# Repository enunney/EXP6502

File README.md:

# EXP6502
6502 based expandable computer.

## Specifications

- W65C02 CPU @ 8MHz
- 64 kB SRAM
- 32 kB EEPROM (read only)
- 7 general purpose expansion ports
- Bank switching with access to up to 160 kB of memory
- W65C22 Versatile Interface Adapter
- Software controllable glitchless clock switching (8 MHz / fraction of 8 MHz)
- Built-in beeper speaker and LED
- 5 built-in push buttons with interrupt capability

## Architecture
### Block diagram

The CPU address and data buses are directly connected to the onboard memory and peripherals. Tristate buffers isolate the local buses from the expansion ports.
CMOS logic ICs decode the address bus as well as the status of the control register to provide control signals for each component.

### Memory map

The lower half of the address space contains 32 kB of RAM (the low RAM) and the I/O space. The I/O space sits
between $6000 and $6FFF. It can be switched out to access the 4 kB of RAM located at the same memory addresses.

The I/O space is made of two parts. The bottom one is divided in 8 pages, each of these controlling one I/O
peripheral. The first I/O page is reserved for the built in VIA. The 7 others are each attributed to a different
expansion port. The top part of the I/O space, IOH, is available on every expansion port, in case they need more I/O
addresses.

The upper half of the address space is divided in two blocks, each of them is multiplied in 4 banks. One bank in each
block can be selected at a time, and the two blocks can have a different bank selected.

The first bank gives access to the ROM of the computer, it is selected by default at start up or after reset.
The second one gives access to 32 kB of RAM, the high RAM.
The third and fourth ones give access to memory placed on the expansion ports. The chip select signals of these
banks are accessible on any expansion port.

The bank switching in the lower half of the address space is controlled by the RIO signal, bit 3 of the control register.
It allows switching the window between $6000 and $6FFF to the I/O space, when RIO is low, or to the low RAM,
when RIO is high.

The bank switching in the upper half of the address space is controlled by the LB0, LB1, HB0 and HB1 signals, bits 4 to
7 of the control register. The bits LB0 and LB1 control the bank switching in the bottom block (\$8000 to \$BFFF). HB0
and HB1 control the switching in the top block (\$C000 to \$FFFF).
- The first bank, bank 0, is mapped to the ROM, in the two blocks.
- The bank 1, is mapped in the two blocks to the high RAM.
- The bank 2 enables the external high memory 0, EXT0HI in the top block and the external low memory 0, EXT0LO in the bottom block.
- The bank 3 enables the external high memory 1, EXT1HI in the top block and the external low memory 1, EXT1LO in the bottom block.

### Expansion port

The computer has 7 general purpose expansion ports.
They give access to buffered versions of the address and data buses of the computer, to various control signals of
the microprocessor and to the selecting signals for the external memory banks. They also have access to some pins
of the VIA.

The expansion ports have access to the main clock, φ2, as well as the oscillator clock and the divided clock. This
feature allows an expansion card to keep using one of these clocks while the computer has switched to another one,
for instance for slow peripherals that couldn’t handle the oscillator frequency. It is worth noting that the CPU can’t
access these peripherals while the clocks are different, as it would have an unpredictable behavior.

Any expansion port can take control of the computer, by setting low the EXTCTLB signal, which disables the busses of
the CPU and reverses the direction of the address and data buffers. The RDY signal should be put low at the same
time to effectively halt the CPU.

The expansion port 1 has an additional two pins header socket placed next to it. It is intended to be connected to the
read and write pins of a TFT LCD screen (controlled by an ILI9341 IC or compatible) for write only access when the
port 1 is connected to such a screen.

The pinout of the expansion ports and the function of each pin can be found in the technical reference manual.

### Control register

The control register allows the software to switch the memory banks, to change the clock speed and to directly
control an LED and the beeper speaker.
It is located at address $0000 of the address space, in the zero page of the 6502 microprocessor, to allow faster
access.
The function of each of its bits is given below:

- Bit 0: CPULED
→ Control signal for the built in LED.
- Bit 1: CPUSPK
→ Can be connected to the built in beeper speaker.
- Bit 2: SELCLK
→ Control the current clock source for the main clock φ2.
- Bit 3: RIO
→ Select the I/O space or the low RAM between $6000 and $6FFF.
- Bit 4: LB0
→ LSB of the number of the selected bank in the bottom block of the upper half of the address space.
- Bit 5: LB1
→ MSB of the number of the selected bank in the bottom block of the upper half of the address space.
- Bit 6: HB0
→ LSB of the number of the selected bank in the top block of the upper half of the address space.
- Bit 7: HB1
→ MSB of the number of the selected bank in the top block of the upper half of the address space.

More details are available in the technical reference manual.

### Clocking

The main clock of the computer, φ2, can be switched between two different sources: the oscillator clock or a divided
version of the oscillator clock.

The default oscillator frequency is 8 MHz. A counter and a JK flip-flop generate a divided version of this clock. The
dividing ratio can be configured with 4 jumpers on the computer. The ratio is between /2 when the value configured
by the jumpers is set to 15, and /32 when the value is 0.
The dividing ratio follows the formula: R = 2*(16-n), where n is the value configured with the jumpers.

The oscillator clock can also be replaced by an external clock, placed on any of the expansion port. The external clock
must be selected with the corresponding jumper.

### I/O

The computer has a built in Versatile Interface Adapter (VIA), of which the two GPIO ports are accessible on 2 pin
header sockets. The CA1, CA2, CB1 and CB2 pins of the VIA are accessible on another pin header socket, as well as on
every expansion port.

The bits 3, 4 and 5 of the PORT B of the VIA can be connected to an 8 to 3 priority encoder with jumpers. The inputs
of the encoder are driven by 5 push buttons. When a button is pressed, the corresponding code is sent to the VIA.
The encoder can generate an interrupt either directly or through the CA2 pin of the VIA, depending on the jumper
configuration.

The VIA can also drive the built in beeper speaker when the jumper connected to the speaker is set accordingly.
The control register is connected to the red LED and can be connected to the speaker.

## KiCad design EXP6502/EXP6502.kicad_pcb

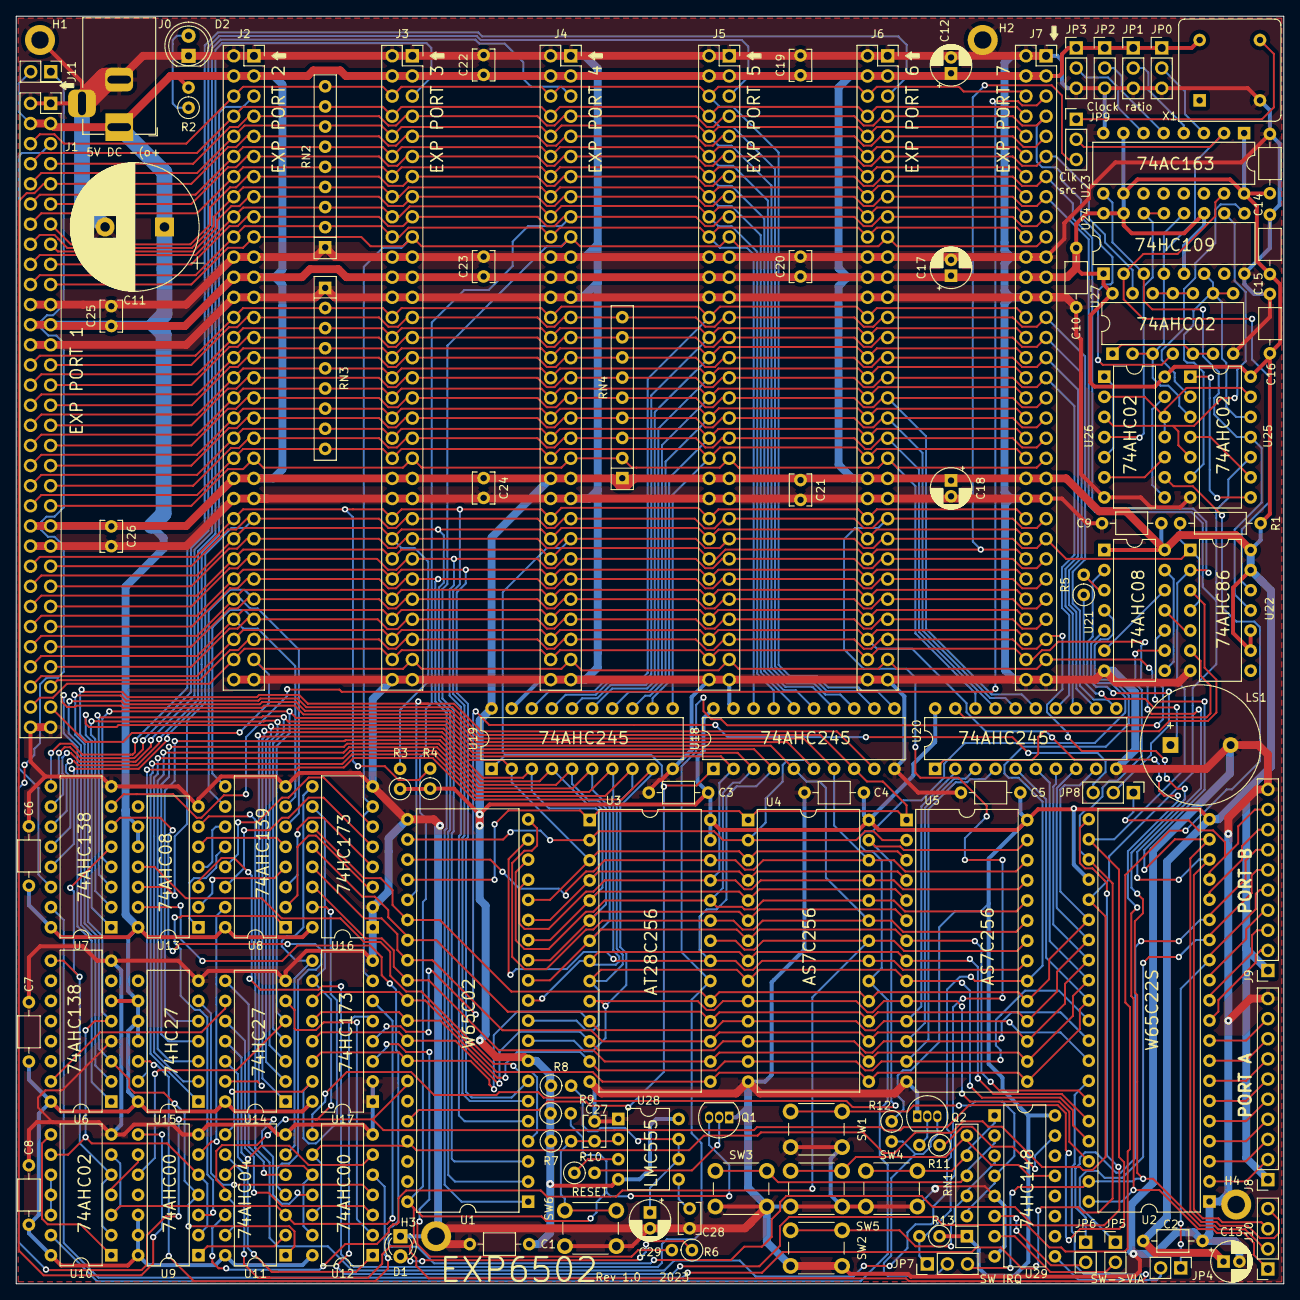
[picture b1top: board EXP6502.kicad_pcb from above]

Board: 2 copper layers, 160.0 x 160.0 mm, 113 parts (0 on the bottom side), 182 nets.

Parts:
C1, C2, C3, C4, C5, C6, C7, C8, C9, C10, C14, C15, C16: 100n; C_Axial_L3.8mm_D2.6mm_P7.50mm_Horizontal
C11: 2200u; CP_Radial_D16.0mm_P7.50mm
C12, C13, C17, C18: 10u; CP_Radial_D5.0mm_P2.00mm
C19, C20, C21, C22, C23, C24, C25, C26, C27: 100n; C_Disc_D3.8mm_W2.6mm_P2.50mm
C28: 10n; C_Disc_D3.8mm_W2.6mm_P2.50mm
C29: 4.7u; CP_Radial_D5.0mm_P2.00mm
D1: LED; LED_D3.0mm
D2: LED; LED_D5.0mm
H1, H2, H3, H4: MountingHole_Pad; MountingHole_2.2mm_M2_DIN965_Pad
J0: Barrel_Jack_Switch; BarrelJack_Horizontal
J1, J2, J3, J4, J5, J6, J7: Conn_02x32_Odd_Even; PinSocket_2x32_P2.54mm_Vertical
J8, J9: Conn_01x10; PinSocket_1x10_P2.54mm_Vertical
J10: Conn_01x04; PinSocket_1x04_P2.54mm_Vertical
J11: Conn_02x01; PinSocket_2x01_P2.54mm_Vertical
JP0, JP1, JP2, JP3, JP7, JP8, JP9: Jumper_3_Bridged12; PinHeader_1x03_P2.54mm_Vertical
JP4, JP5, JP6: Jumper_2_Bridged; PinHeader_1x02_P2.54mm_Vertical
LS1: Speaker; Buzzer_15x7.5RM7.6
Q1, Q2: 2N7000; TO-92_Inline
R1: 10k; R_Axial_DIN0207_L6.3mm_D2.5mm_P10.16mm_Horizontal
R2, R6, R10, R11: 1k; R_Axial_DIN0207_L6.3mm_D2.5mm_P2.54mm_Vertical
R3, R4, R9, R12, R13: 10k; R_Axial_DIN0207_L6.3mm_D2.5mm_P2.54mm_Vertical
R5: 470; R_Axial_DIN0207_L6.3mm_D2.5mm_P2.54mm_Vertical
R7: 1M; R_Axial_DIN0207_L6.3mm_D2.5mm_P2.54mm_Vertical
R8: 47k; R_Axial_DIN0207_L6.3mm_D2.5mm_P2.54mm_Vertical
RN1: R_Network05_US; R_Array_SIP6
RN2, RN3, RN4: R_Network08_US; R_Array_SIP9
SW1, SW2, SW3, SW4, SW5, SW6: SW_Push; SW_PUSH_6mm
U1: W65C02SxP; DIP-40_W15.24mm
U2: W65C22SxP; DIP-40_W15.24mm
U3: 28C256; DIP-28_W15.24mm
U4, U5: CY62256-70PC; DIP-28_W15.24mm
U6, U7: 74LS138; DIP-16_W7.62mm
U8: 74LS139; DIP-16_W7.62mm
U9, U12: 74HC00; DIP-14_W7.62mm
U10, U25, U26, U27: 74HC02; DIP-14_W7.62mm
U11: 74AHC04; DIP-14_W7.62mm
U13, U21: 74LS08; DIP-14_W7.62mm
U14, U15: 74LS27; DIP-14_W7.62mm
U16, U17: 74LS173; DIP-16_W7.62mm
U18, U19, U20: 74HC245; DIP-20_W7.62mm
U22: 74LS86; DIP-14_W7.62mm
U23: 74LS163; DIP-16_W7.62mm
U24: 74LS109; DIP-16_W7.62mm
U28: LMC555xN; DIP-8_W7.62mm
U29: 74LS148; DIP-16_W7.62mm
X1: TFT660; Oscillator_DIP-8

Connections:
/AddressDecoding/CTLREGB: U11.6, U16.9 (E1), U17.9 (E1)
/AddressDecoding/HB0: U8.14 (A0), U16.5 (Q2)
/AddressDecoding/HB1: U8.13 (A1), U16.6 (Q3)
/AddressDecoding/LB0: U8.2 (A0), U16.3 (Q0)
/AddressDecoding/LB1: U8.3 (A1), U16.4 (Q1)
/AddressDecoding/RIO: U10.3, U10.6, U11.3, U17.6 (Q3)
A0: U1.9 (A0), U2.38 (RS0), U3.10 (A0), U4.10 (A0), U5.10 (A0), U15.13, U19.9 (A7)
A1: U1.10 (A1), U2.37 (RS1), U3.9 (A1), U4.9 (A1), U5.9 (A1), U15.1, U19.8 (A6)
A2: U1.11 (A2), U2.36 (RS2), U3.8 (A2), U4.8 (A2), U5.8 (A2), U15.2, U19.7 (A5)
A3: U1.12 (A3), U2.35 (RS3), U3.7 (A3), U4.7 (A3), U5.7 (A3), U15.3, U19.6 (A4)
A4: U1.13 (A4), U3.6 (A4), U4.6 (A4), U5.6 (A4), U15.4, U19.5 (A3)
A5: U1.14 (A5), U3.5 (A5), U4.5 (A5), U5.5 (A5), U15.5, U19.4 (A2)
A6: U1.15 (A6), U3.4 (A6), U4.4 (A6), U5.4 (A6), U14.13, U19.3 (A1)
A7: U1.16 (A7), U3.3 (A7), U4.3 (A7), U5.3 (A7), U14.1, U19.2 (A0)
A8: U1.17 (A8), U3.25 (A8), U4.25 (A8), U5.25 (A8), U7.1 (A0), U14.2, U18.2 (A0)
A9: U1.18 (A9), U3.24 (A9), U4.24 (A9), U5.24 (A9), U7.2 (A1), U14.3, U18.3 (A1)
A10: U1.19 (A10), U3.21 (A10), U4.21 (A10), U5.21 (A10), U7.3 (A2), U14.4, U18.4 (A2)
A11: U1.20 (A11), U3.23 (A11), U4.23 (A11), U5.23 (A11), U7.4 (E1), U9.10, U14.5, U18.5 (A3)
A12: U1.22 (A12), U3.2 (A12), U4.2 (A12), U5.2 (A12), U6.1 (A0), U18.6 (A4)
A13: U1.23 (A13), U3.26 (A13), U4.26 (A13), U5.26 (A13), U6.2 (A1), U18.7 (A5)
A14: U1.24 (A14), U3.1 (A14), U4.1 (A14), U5.1 (A14), U6.3 (A2), U9.4, U11.1, U18.8 (A6)
A15: U1.25 (A15), U6.5 (E2), U9.2, U9.5, U10.9, U18.9 (A7)
AE0: J1.42, J2.42, J3.42, J4.42, J5.42, J6.42, J7.42, RN3.9 (R8), U19.11 (B7)
AE1: J1.40, J2.40, J3.40, J4.40, J5.40, J6.40, J7.40, RN3.8 (R7), U19.12 (B6)
AE2: J1.38, J2.38, J3.38, J4.38, J5.38, J6.38, J7.38, RN3.7 (R6), U19.13 (B5)
AE3: J1.36, J2.36, J3.36, J4.36, J5.36, J6.36, J7.36, RN3.6 (R5), U19.14 (B4)
AE4: J1.34, J2.34, J3.34, J4.34, J5.34, J6.34, J7.34, RN3.5 (R4), U19.15 (B3)
AE5: J1.32, J2.32, J3.32, J4.32, J5.32, J6.32, J7.32, RN3.4 (R3), U19.16 (B2)
AE6: J1.30, J2.30, J3.30, J4.30, J5.30, J6.30, J7.30, RN3.3 (R2), U19.17 (B1)
AE7: J1.28, J2.28, J3.28, J4.28, J5.28, J6.28, J7.28, RN3.2 (R1), U19.18 (B0)
AE8: J1.20, J2.20, J3.20, J4.20, J5.20, J6.20, J7.20, RN2.2 (R1), U18.18 (B0)
AE9: J1.18, J2.18, J3.18, J4.18, J5.18, J6.18, J7.18, RN2.3 (R2), U18.17 (B1)
AE10: J1.16, J2.16, J3.16, J4.16, J5.16, J6.16, J7.16, RN2.4 (R3), U18.16 (B2)
AE11: J1.14, J2.14, J3.14, J4.14, J5.14, J6.14, J7.14, RN2.5 (R4), U18.15 (B3)
AE12: J1.12, J2.12, J3.12, J4.12, J5.12, J6.12, J7.12, RN2.6 (R5), U18.14 (B4)
AE13: J1.10, J2.10, J3.10, J4.10, J5.10, J6.10, J7.10, RN2.7 (R6), U18.13 (B5)
AE14: J1.8, J2.8, J3.8, J4.8, J5.8, J6.8, J7.8, RN2.8 (R7), U18.12 (B6)
AE15: J1.6, J2.6, J3.6, J4.6, J5.6, J6.6, J7.6, RN2.9 (R8), U18.11 (B7)
CA1: J1.60, J2.60, J3.60, J4.60, J5.60, J6.60, J7.60, J10.1, U2.40 (CA1)
CA2: J1.59, J2.59, J3.59, J4.59, J5.59, J6.59, J7.59, J10.2, JP7.3 (B), U2.39 (CA2)
CB1: J1.62, J2.62, J3.62, J4.62, J5.62, J6.62, J7.62, J10.3, U2.18 (CB1)
CB2: J1.61, J2.61, J3.61, J4.61, J5.61, J6.61, J7.61, J10.4, U2.19 (CB2)
CLKDIV: J1.11, J2.11, J3.11, J4.11, J5.11, J6.11, J7.11, U27.13
CLKOSC: J1.7, J2.7, J3.7, J4.7, J5.7, J6.7, J7.7, U27.4
CPULED: R6.2, U17.3 (Q0)
CPUSPK: JP8.3 (B), U17.4 (Q1)
D0: U1.33 (D0), U2.33 (D0), U3.11 (D0), U4.11 (Q0), U5.11 (Q0), U17.14 (D0), U20.2 (A0)
D1: U1.32 (D1), U2.32 (D1), U3.12 (D1), U4.12 (Q1), U5.12 (Q1), U17.13 (D1), U20.3 (A1)
D2: U1.31 (D2), U2.31 (D2), U3.13 (D2), U4.13 (Q2), U5.13 (Q2), U17.12 (D2), U20.4 (A2)
D3: U1.30 (D3), U2.30 (D3), U3.15 (D3), U4.15 (Q3), U5.15 (Q3), U17.11 (D3), U20.5 (A3)
D4: U1.29 (D4), U2.29 (D4), U3.16 (D4), U4.16 (Q4), U5.16 (Q4), U16.14 (D0), U20.6 (A4)
D5: U1.28 (D5), U2.28 (D5), U3.17 (D5), U4.17 (Q5), U5.17 (Q5), U16.13 (D1), U20.7 (A5)
D6: U1.27 (D6), U2.27 (D6), U3.18 (D6), U4.18 (Q6), U5.18 (Q6), U16.12 (D2), U20.8 (A6)
D7: U1.26 (D7), U2.26 (D7), U3.19 (D7), U4.19 (Q7), U5.19 (Q7), U16.11 (D3), U20.9 (A7)
DE0: J1.41, J2.41, J3.41, J4.41, J5.41, J6.41, J7.41, RN4.2 (R1), U20.18 (B0)
DE1: J1.39, J2.39, J3.39, J4.39, J5.39, J6.39, J7.39, RN4.3 (R2), U20.17 (B1)
DE2: J1.37, J2.37, J3.37, J4.37, J5.37, J6.37, J7.37, RN4.4 (R3), U20.16 (B2)
DE3: J1.35, J2.35, J3.35, J4.35, J5.35, J6.35, J7.35, RN4.5 (R4), U20.15 (B3)
DE4: J1.33, J2.33, J3.33, J4.33, J5.33, J6.33, J7.33, RN4.6 (R5), U20.14 (B4)
DE5: J1.31, J2.31, J3.31, J4.31, J5.31, J6.31, J7.31, RN4.7 (R6), U20.13 (B5)
DE6: J1.29, J2.29, J3.29, J4.29, J5.29, J6.29, J7.29, RN4.8 (R7), U20.12 (B6)
DE7: J1.27, J2.27, J3.27, J4.27, J5.27, J6.27, J7.27, RN4.9 (R8), U20.11 (B7)
EXTCLK: J1.52, J2.52, J3.52, J4.52, J5.52, J6.52, J7.52, JP9.3 (B)
EXTCTLB: J1.49, J2.49, J3.49, J4.49, J5.49, J6.49, J7.49, R1.2, U1.36 (BE), U18.1 (A->B), U19.1 (A->B), U22.1, U22.4
EXTH0B: J1.55, J2.55, J3.55, J4.55, J5.55, J6.55, J7.55, U8.10 (O2)
EXTH1B: J1.57, J2.57, J3.57, J4.57, J5.57, J6.57, J7.57, U8.9 (O3)
EXTL0B: J1.56, J2.56, J3.56, J4.56, J5.56, J6.56, J7.56, U8.6 (O2)
EXTL1B: J1.58, J2.58, J3.58, J4.58, J5.58, J6.58, J7.58, U8.7 (O3)
GND: C1.2, C2.2, C3.2, C4.2, C5.2, C6.2, C7.2, C8.2, C9.2, C10.2, C11.2, C12.2, C13.2, C14.2, C15.2, C16.2, C17.2, C18.2, C19.2, C20.2, C21.2, C22.2, C23.2, C24.2, C25.2, C26.2, C27.2, C28.2, C29.2, D1.1 (K), D2.1 (K), H1.1, H2.1, H3.1, H4.1, J0.2, J0.3, J1.1, J1.2, J1.21, J1.22, J1.25, J1.26, J1.45, J1.46, J1.63, J1.64, J2.1, J2.2, J2.21, J2.22, J2.25, J2.26, J2.45, J2.46, J2.63, J2.64, J3.1, J3.2, J3.21, J3.22, J3.25, J3.26, J3.45, J3.46, J3.63, J3.64, J4.1, J4.2, J4.21, J4.22, J4.25, J4.26, J4.45, J4.46, J4.63, J4.64, J5.1, J5.2, J5.21, J5.22, J5.25, J5.26, J5.45, J5.46, J5.63, J5.64, J6.1, J6.2, J6.21, J6.22, J6.25, J6.26, J6.45, J6.46, J6.63, J6.64, J7.1, J7.2, J7.21, J7.22, J7.25, J7.26, J7.45, J7.46, J7.63, J7.64, J8.10, J9.10, JP0.3 (B), JP1.3 (B), JP2.3 (B), JP3.3 (B), LS1.2, Q1.1 (S), Q2.1 (S), RN2.1 (common), RN3.1 (common), SW1.2, SW2.2, SW3.2, SW4.2, SW5.2, SW6.1, U1.21 (VSS), U2.1 (VSS), U3.14 (GND), U4.14 (GND), U5.14 (GND), U6.4 (E1), U6.8 (GND), U7.8 (GND), U8.8 (GND), U9.7 (GND), U10.7 (GND), U11.7 (GND), U12.7 (GND), U13.7 (GND), U14.7 (GND), U15.7 (GND), U16.1 (Oe1), U16.2 (Oe2), U16.8 (GND), U17.1 (Oe1), U17.2 (Oe2), U17.8 (GND), U18.10 (GND), U18.19 (CE), U19.10 (GND), U19.19 (CE), U20.10 (GND), U21.7 (GND), U22.7 (GND), U23.8 (GND), U24.8 (GND), U25.7 (GND), U26.7 (GND), U27.7 (GND), U28.1 (GND), U29.5 (EI), U29.8 (GND), X1.4 (GND)
HIRAMB: U5.20 (~CS), U13.6, U21.4
IO2B: J2.5, U7.13 (O2)
IO3B: J3.5, U7.12 (O3)
IO4B: J4.5, U7.11 (O4)
IO5B: J5.5, U7.10 (O5)
IO6B: J6.5, U7.9 (O6)
IO7B: J7.5, U7.7 (O7)
IOHB: J1.9, J2.9, J3.9, J4.9, J5.9, J6.9, J7.9, U9.8
IRQB: U1.4 (~IRQ), U13.11
IRQEXTB: J1.47, J2.47, J3.47, J4.47, J5.47, J6.47, J7.47, JP7.1 (A), R13.2, U13.12
LORAMB: U4.20 (~CS), U10.13, U21.5
MLB: J1.51, J2.51, J3.51, J4.51, J5.51, J6.51, J7.51, U1.5 (~ML)
NMIB: J1.48, J2.48, J3.48, J4.48, J5.48, J6.48, J7.48, R4.2, U1.6 (~NMI)
unnamed: D1.2 (A), R6.1
unnamed: D2.2 (A), R2.1
unnamed: J8.2, U2.2 (PA0)
unnamed: J8.3, U2.3 (PA1)
unnamed: J8.4, U2.4 (PA2)
unnamed: J8.5, U2.5 (PA3)
unnamed: J8.6, U2.6 (PA4)
unnamed: J8.7, U2.7 (PA5)
unnamed: J8.8, U2.8 (PA6)
unnamed: J8.9, U2.9 (PA7)
unnamed: J9.2, U2.10 (PB0)
unnamed: J9.3, U2.11 (PB1)
unnamed: J9.4, U2.12 (PB2)
unnamed: J9.5, JP4.1 (A), U2.13 (PB3)
unnamed: J9.6, JP5.1 (A), U2.14 (PB4)
unnamed: J9.7, JP6.1 (A), U2.15 (PB5)
unnamed: J9.8, U2.16 (PB6)
unnamed: J9.9, JP8.1 (A), U2.17 (PB7)
unnamed: JP0.2 (C), U23.3 (D0)
unnamed: JP1.2 (C), U23.4 (D1)
unnamed: JP2.2 (C), U23.5 (D2)
unnamed: JP3.2 (C), U23.6 (D3)
unnamed: JP4.2 (B), U29.9 (S0)
unnamed: JP5.2 (B), U29.7 (S1)
unnamed: JP6.2 (B), U29.6 (S2)
unnamed: JP7.2 (C), Q2.3 (D), R12.2
unnamed: JP8.2 (C), U21.2
unnamed: JP9.1 (A), X1.5 (OUT)
unnamed: JP9.2 (C), U23.2 (CP), U24.4 (C), U24.12 (C), U25.3, U27.2, U27.3
unnamed: LS1.1, R5.1
unnamed: Q1.2 (G), R10.2
unnamed: Q2.2 (G), R11.2
unnamed: R5.2, U21.3
unnamed: RN1.2 (R1), SW1.1, U29.4 (I7)
unnamed: RN1.3 (R2), SW2.1, U29.3 (I6)
unnamed: RN1.4 (R3), SW3.1, U29.2 (I5)
unnamed: RN1.5 (R4), SW4.1, U29.1 (I4)
unnamed: RN1.6 (R5), SW5.1, U29.13 (I3)
unnamed: U2.21 (~IRQ), U13.13
unnamed: U6.15 (O0), U14.9
unnamed: U6.9 (O6), U7.5 (E2), U10.2, U10.5
unnamed: U7.6 (E3), U11.4
unnamed: U8.1 (E), U9.3
unnamed: U8.4 (O0), U13.2
unnamed: U8.5 (O1), U13.5
unnamed: U8.15 (E), U9.6
unnamed: U8.12 (O0), U13.1
unnamed: U8.11 (O1), U13.4
unnamed: U10.1, U10.8
unnamed: U9.9, U10.4
unnamed: U10.10, U10.11, U10.12
unnamed: U9.1, U11.2
unnamed: U11.5, U14.8
unnamed: U11.10, U12.10, U12.13
unnamed: U12.1, U14.12
unnamed: U12.2, U14.6
unnamed: U12.3, U14.10
unnamed: U12.4, U15.6
unnamed: U12.5, U15.12
unnamed: U12.6, U14.11
unnamed: U11.8, U16.15 (Mr), U17.15 (Mr)
unnamed: U20.1 (A->B), U22.3
unnamed: U20.19 (CE), U22.6
unnamed: U21.11, U22.5
unnamed: U21.6, U21.12
unnamed: U21.8, U21.13
unnamed: U22.12, U23.15 (TC), U24.2 (J)
unnamed: U22.11, U23.9 (~PE), U24.3 (~K), U25.11
unnamed: U24.6 (Q), U25.6, U25.12, U27.8, U27.9
unnamed: U24.13 (~K), U24.14 (J), U26.4
unnamed: U24.10 (Q), U25.5, U26.3
unnamed: U24.9 (~Q), U25.2
unnamed: U25.1, U25.8
unnamed: U25.4, U25.9
unnamed: U25.13, U26.2, U26.11, U26.12
unnamed: U26.1, U26.5
unnamed: U26.6, U26.10
unnamed: U26.8, U26.13
unnamed: U27.1, U27.5, U27.6
unnamed: U27.10, U27.11, U27.12
unnamed: C28.1, U28.5 (CV)
unnamed: C29.1, R8.2, U28.6 (THR), U28.7 (DIS)
unnamed: R10.1, U28.3 (Q)
unnamed: C27.1, R7.2, SW6.2, U28.2 (TR)
unnamed: R11.1, U29.15 (EO)
PHI1: J1.19, J2.19, J3.19, J4.19, J5.19, J6.19, J7.19, U1.3 (ϕ1), U16.7 (Cp), U17.7 (Cp)
PHI2: J1.15, J2.15, J3.15, J4.15, J5.15, J6.15, J7.15, U1.37 (ϕ0), U2.25 (ϕ2), U12.9, U12.12, U25.10
RDY: J1.50, J2.50, J3.50, J4.50, J5.50, J6.50, J7.50, R3.2, U1.2 (RDY)
ROMB: U3.20 (~CS), U13.3, U21.10
RSTB: J1.17, J2.17, J3.17, J4.17, J5.17, J6.17, J7.17, Q1.3 (D), R9.2, U1.40 (~RES), U2.34 (~RES), U11.9
RW: J1.13, J2.13, J3.13, J4.13, J5.13, J6.13, J7.13, U1.34 (R/~W), U2.22 (R/~W), U11.11, U11.13, U16.10 (E2), U17.10 (E2), U22.2
RWB: U3.22 (~OE), U4.22 (~OE), U5.22 (~OE), U11.12
SELCLK: U17.5 (Q2), U26.9
SYNC: J1.54, J2.54, J3.54, J4.54, J5.54, J6.54, J7.54, U1.7 (SYNC)
TFTB: J1.5, U7.14 (O1)
VDD: C1.1, C2.1, C3.1, C4.1, C5.1, C6.1, C7.1, C8.1, C9.1, C10.1, C11.1, C12.1, C13.1, C14.1, C15.1, C16.1, C17.1, C18.1, C19.1, C20.1, C21.1, C22.1, C23.1, C24.1, C25.1, C26.1, J0.1, J1.3, J1.4, J1.23, J1.24, J1.43, J1.44, J2.3, J2.4, J2.23, J2.24, J2.43, J2.44, J3.3, J3.4, J3.23, J3.24, J3.43, J3.44, J4.3, J4.4, J4.23, J4.24, J4.43, J4.44, J5.3, J5.4, J5.23, J5.24, J5.43, J5.44, J6.3, J6.4, J6.23, J6.24, J6.43, J6.44, J7.3, J7.4, J7.23, J7.24, J7.43, J7.44, J8.1, J9.1, J11.2, JP0.1 (A), JP1.1 (A), JP2.1 (A), JP3.1 (A), R1.1, R2.2, R3.1, R4.1, R7.1, R8.1, R9.1, R12.1, R13.1, RN1.1 (common), RN4.1 (common), U1.8 (VDD), U2.20 (VCC), U2.24 (CS1), U3.27 (~WE), U3.28 (VCC), U4.28 (VCC), U5.28 (VCC), U6.6 (E3), U6.16 (VCC), U7.16 (VCC), U8.16 (VCC), U9.12, U9.13, U9.14 (VCC), U10.14 (VCC), U11.14 (VCC), U12.14 (VCC), U13.9, U13.10, U13.14 (VCC), U14.14 (VCC), U15.9, U15.10, U15.11, U15.14 (VCC), U16.16 (VCC), U17.16 (VCC), U18.20 (VCC), U19.20 (VCC), U20.20 (VCC), U21.1, U21.14 (VCC), U22.9, U22.10, U22.13, U22.14 (VCC), U23.1 (~MR), U23.7 (CEP), U23.10 (CET), U23.16 (VCC), U24.1 (~R), U24.5 (~S), U24.11 (~S), U24.15 (~R), U24.16 (VCC), U25.14 (VCC), U26.14 (VCC), U27.14 (VCC), U28.4 (R), U28.8 (VCC), U29.16 (VCC), X1.8 (Vcc)
VIAB: U2.23 (~CS2), U7.15 (O0), U21.9
VPB: J1.53, J2.53, J3.53, J4.53, J5.53, J6.53, J7.53, U1.1 (~VP)
WRAMB: U4.27 (~WE), U5.27 (~WE), U12.8
WTFTB: J11.1, U12.11

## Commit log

2025-03-15 init commit
2025-03-16 readme
